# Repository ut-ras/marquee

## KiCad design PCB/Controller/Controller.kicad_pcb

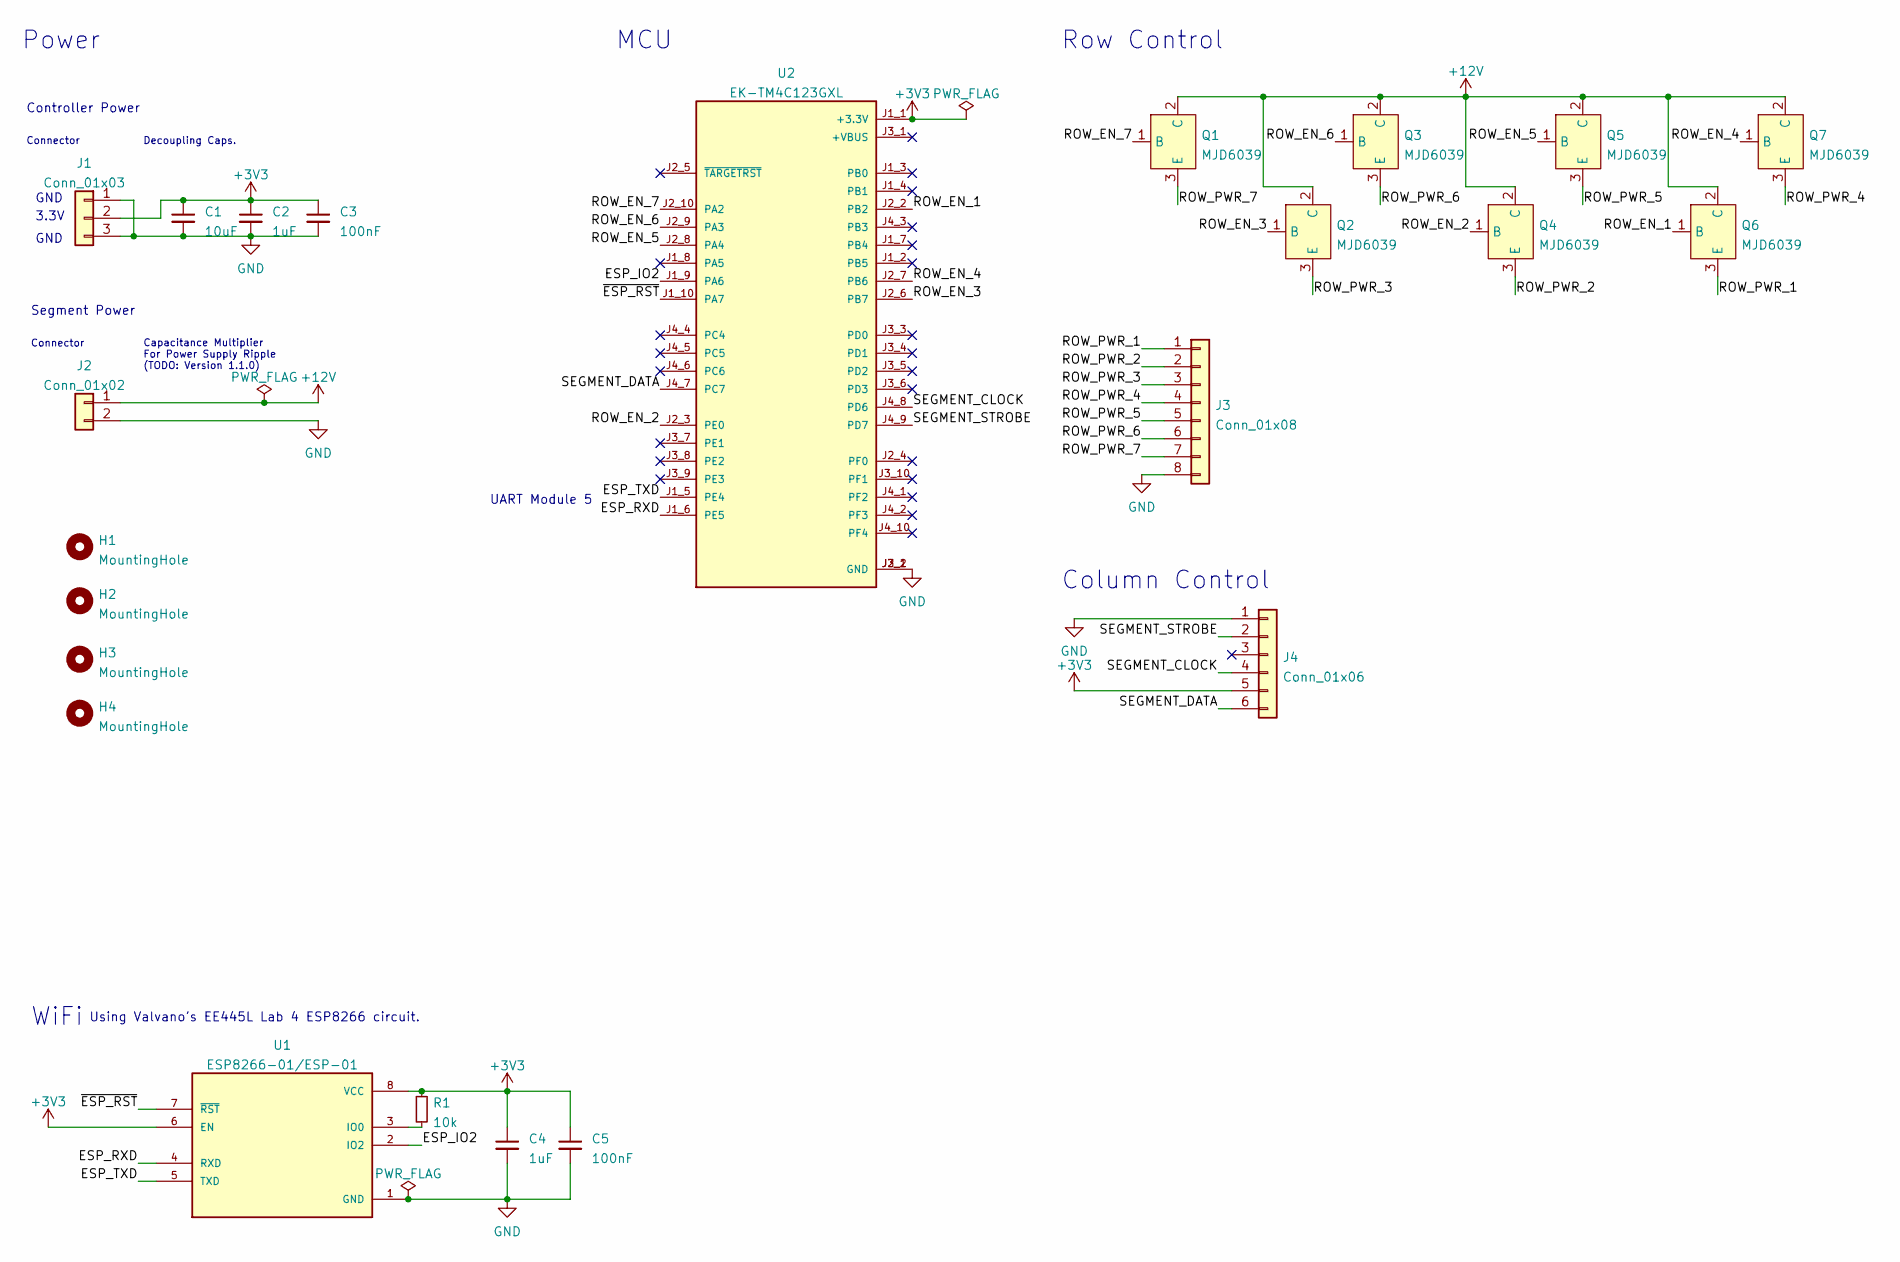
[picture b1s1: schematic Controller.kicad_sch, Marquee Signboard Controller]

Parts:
C1: 10uF; C_0805_2012Metric; Part Number CL21A106KAYNNNE; JLCPCB BOM 1
C2, C4: 1uF; C_0805_2012Metric; Part Number CL21B105KBFNNNE; JLCPCB BOM 1
C3, C5: 100nF; C_0805_2012Metric; Part Number CC0805KRX7R9BB104; JLCPCB BOM 1
H1, H2, H3, H4: MountingHole; MountingHole_2.2mm_M2
J1: Conn_01x03; PinHeader_1x03_P2.54mm_Vertical
J2: Conn_01x02; SolderWire-2.5sqmm_1x02_P7.2mm_D2.4mm_OD3.6mm
J3: Conn_01x08; SolderWire-2sqmm_1x08_P7.8mm_D2mm_OD3.9mm
J4: Conn_01x06; SolderWire-2.5sqmm_1x06_P8.8mm_D2.4mm_OD4.4mm
Q1, Q2, Q3, Q4, Q5, Q6, Q7: MJD6039; TO-252-3_TabPin2; Part Number MJD6039T4G; JLCPCB BOM 0
R1: 10k; R_0805_2012Metric; Part Number 0805W8F510KT5E; JLCPCB BOM 1
U1: ESP8266-01/ESP-01; XCVR_ESP8266-01_ESP-01; Part Number WRL-17146; JLCPCB BOM 0
U2: EK-TM4C123GXL; MODULE_EK-TM4C123GXL; Part Number EK-TM4C123GXL; JLCPCB BOM 0

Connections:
+3V3: C1.1, C2.1, C3.1, C4.1, C5.1, J1.2, J4.5, R1.1, U1.6 (EN), U1.8 (VCC), U2.J1_1 (+3.3V)
+12V: J2.1, Q1.2 (C), Q2.2 (C), Q3.2 (C), Q4.2 (C), Q5.2 (C), Q6.2 (C), Q7.2 (C)
/ESP_IO2: U1.2 (IO2), U2.J1_9 (PA6)
/ESP_RXD: U1.4 (RXD), U2.J1_6 (PE5)
/ESP_TXD: U1.5 (TXD), U2.J1_5 (PE4)
/ROW_EN_1: Q6.1 (B), U2.J2_2 (PB2)
/ROW_EN_2: Q4.1 (B), U2.J2_3 (PE0)
/ROW_EN_3: Q2.1 (B), U2.J2_6 (PB7)
/ROW_EN_4: Q7.1 (B), U2.J2_7 (PB6)
/ROW_EN_5: Q5.1 (B), U2.J2_8 (PA4)
/ROW_EN_6: Q3.1 (B), U2.J2_9 (PA3)
/ROW_EN_7: Q1.1 (B), U2.J2_10 (PA2)
/ROW_PWR_1: J3.1, Q6.3 (E)
/ROW_PWR_2: J3.2, Q4.3 (E)
/ROW_PWR_3: J3.3, Q2.3 (E)
/ROW_PWR_4: J3.4, Q7.3 (E)
/ROW_PWR_5: J3.5, Q5.3 (E)
/ROW_PWR_6: J3.6, Q3.3 (E)
/ROW_PWR_7: J3.7, Q1.3 (E)
/SEGMENT_CLOCK: J4.4, U2.J4_8 (PD6)
/SEGMENT_DATA: J4.6, U2.J4_7 (PC7)
/SEGMENT_STROBE: J4.2, U2.J4_9 (PD7)
/~ESP_RST: U1.7 (~RST), U2.J1_10 (PA7)
GND: C1.2, C2.2, C3.2, C4.2, C5.2, J1.1, J1.3, J2.2, J3.8, J4.1, U1.1 (GND), U2.J2_1 (GND), U2.J3_2 (GND)
unnamed: R1.2, U1.3 (IO0)

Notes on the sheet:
Controller Power
Row Control
Connector
Column Control
Capacitance Multiplier For Power Supply Ripple (TODO: Version 1.1.0)
GND
Decoupling Caps.
Using Valvano's EE445L Lab 4 ESP8266 circuit.
UART Module 5
Segment Power
3.3V
Power
MCU
WiFi

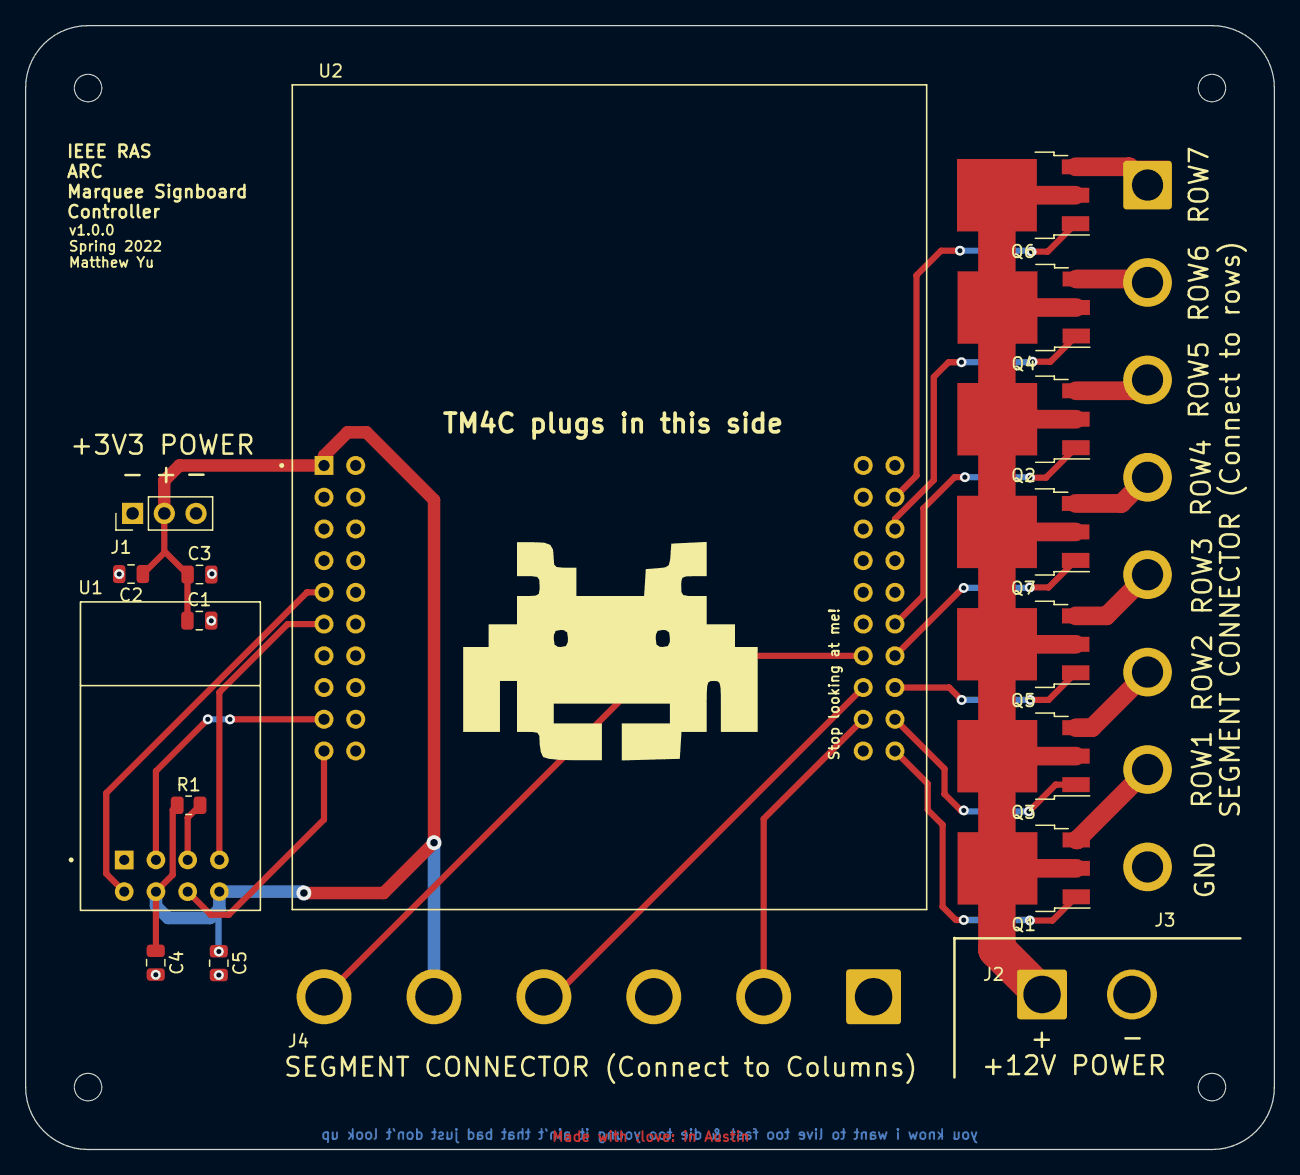
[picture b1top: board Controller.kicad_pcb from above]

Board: 2 copper layers, 100.0 x 90.0 mm, 23 parts (0 on the bottom side), 25 nets.

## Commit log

2015-04-16 Moved everything into a seperate repo not containing all of rasware
2015-04-16 Added text rendering
2015-04-16 Fixed issues with fonts and displaying long messages
2015-05-05 Added actual buffer check
2015-09-24 Added some other changes to make Marquee keep working
2017-12-01 Update makefile for the new world
    The only real change here is that the library search dirs are back in the linker flags (same as current Rasware). Not sure how/why this wasn't already the case.
    Also, Stellaris should be in /usr/local/lib/StellarisWare (same as Rasware)
2017-12-01 Tweaked main.c to: End on any character not defined in the font (instead of waiting for a return carriage - most computers aren't typewriters). Newlines should end messages now. Send the recieved cha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
    It's possible there was some reason why '\r' was used to terminate a message, but I can't think of one.
2017-12-08 started raspi slack listener
2017-12-08 setting up slack channel
2017-12-08 slack api working
2017-12-08 removed token
2017-12-08 started uart function
2017-12-08 added serial stuff
2017-12-08 wiringpi2 import
2017-12-08 uart working
2017-12-09 fixed uart
2018-11-17 ESP01 web server input to the TM4C
2018-11-18 Comments showing how to use UART1 for ESP8266 connection
2018-11-21 Added a clock feature
    Clock only on when signboard is in station mode (connected to WiFi, not broadcasting an AP) because it syncs the time with the internet. clock.h from demobots ESP8266_Arduino_Examples repo
2022-03-31 initial drivers for marquee. needs testing.
2022-03-31 Compiles, segment example ready for testing.
2022-04-01 font work
2022-04-01 hey it kinda works now
2022-04-01 Segment strobing.
2022-04-01 rows are broken.. i blame hardware.
2022-04-01 starting python scripts for bdf conversion.
2022-04-02 Working on bdf parser, new controller PCB.
2022-04-03 sample bdf font script.
2022-04-04 finished v1.0.0 of marquee controller.
2022-04-08 Working segment example. onto font.
2022-04-08 LinearDipsplayPushChar
    Should work maybe to push a defined character onto segment.
2022-04-08 Update Linear Display.c
    Modified LinearDisplayPushChar
2022-04-08 linear display test.
2022-04-12 Updated LinearDisplayPushChar.c
    Added offset for 5-height characters and spaces between characters for readability.
2022-04-14 discord bot code - needs testing
2022-04-14 move the discord_bot file location - still needs testing
2022-04-14 discord bot README
2022-04-14 added gitignore for the discord bot directory
2022-04-15 Playing w/ multiplexing
2022-04-24 latest update of pcbs
2022-04-24 moved discord_bot directory to root and created the ESP directory
2022-04-24 moving directories around
2022-04-24 ESP directory
2022-08-26 savestate boardchange
